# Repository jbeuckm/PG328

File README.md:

# PG328

Program your JX8P/JX10/MKS70 with sliders or MIDI Sysex with this Atmega328 based PG800 variation.

A .96" OLED screen [(buy it here!)](https://amzn.to/4naLiou) shows the status and parameter values and a rotary encoder with momentary push switch provides full PG800 interface capabilities.

### MID SYSEX

#### Prefix: 

* 0x41 // manufacturer ID
* 0x36 // IPR mode
* 0x01 // device ID
* 0x24 // (from MKS70)
* 0x20 // (from MKS70)

#### Suffix:

* 0x01 // Tone

* 0x0F: Reset potentiometer assignments.

### Status:

* 2/24/17: 8-slider pcb tested. This verifies that lots of sliders can work together and will serve as ADSR for EG1 and 2.

* 12/9/16: All Parameters select and display values according to their type. Some even have lil icons...

* 12/7/16: New Sysex message to clear all pot assignments

* 12/3/16: Stable control with encoder. Hold button to rotate parameter or just rotate to change value. Hold button down three seconds to assign slider of highest value to the current parameter.

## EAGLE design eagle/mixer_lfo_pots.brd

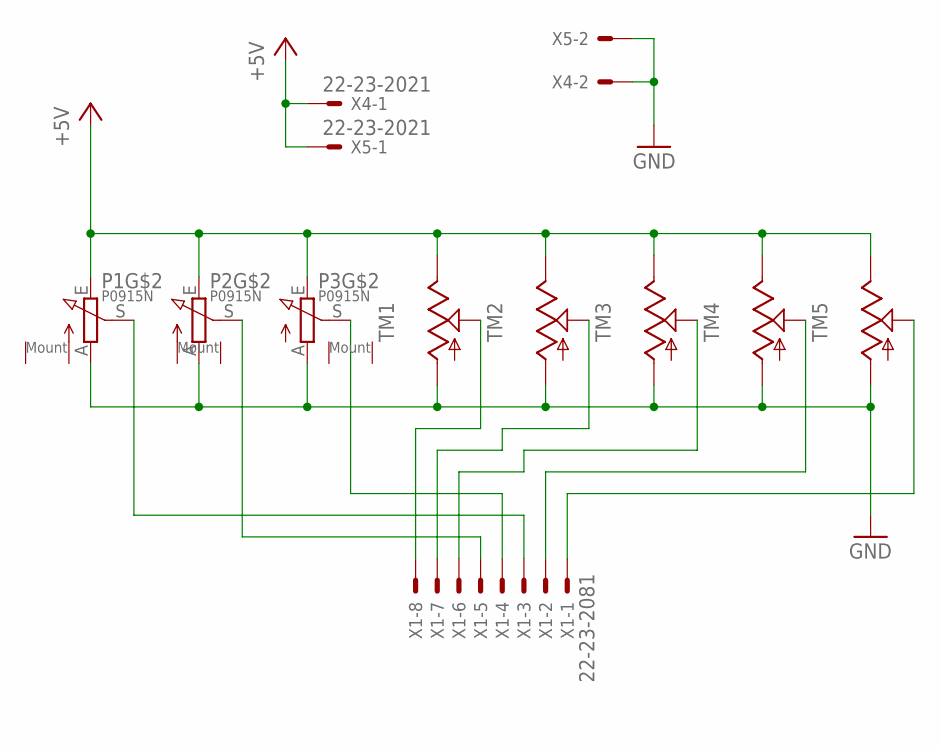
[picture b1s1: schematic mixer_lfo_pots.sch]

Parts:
P1, P2, P3: P0915N
TM1, TM2, TM3, TM4, TM5: TRIMSLIDE60; SLIDEPOT-60
X1: 22-23-2081
X4, X5: 22-23-2021

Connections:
+5V: P1.E, P2.E, P3.E, TM1.B, TM2.B, TM3.B, TM4.B, TM5.B, X4.1, X5.1
GND: P1.A, P2.A, P3.A, TM1.A, TM2.A, TM3.A, TM4.A, TM5.A, X4.2, X5.2
unnamed: P1.S, X1.3
unnamed: P2.S, X1.5
unnamed: P3.S, X1.4
unnamed: TM1.WIPER, X1.8
unnamed: TM2.WIPER, X1.7
unnamed: TM3.WIPER, X1.6
unnamed: TM4.WIPER, X1.2
unnamed: TM5.WIPER, X1.1

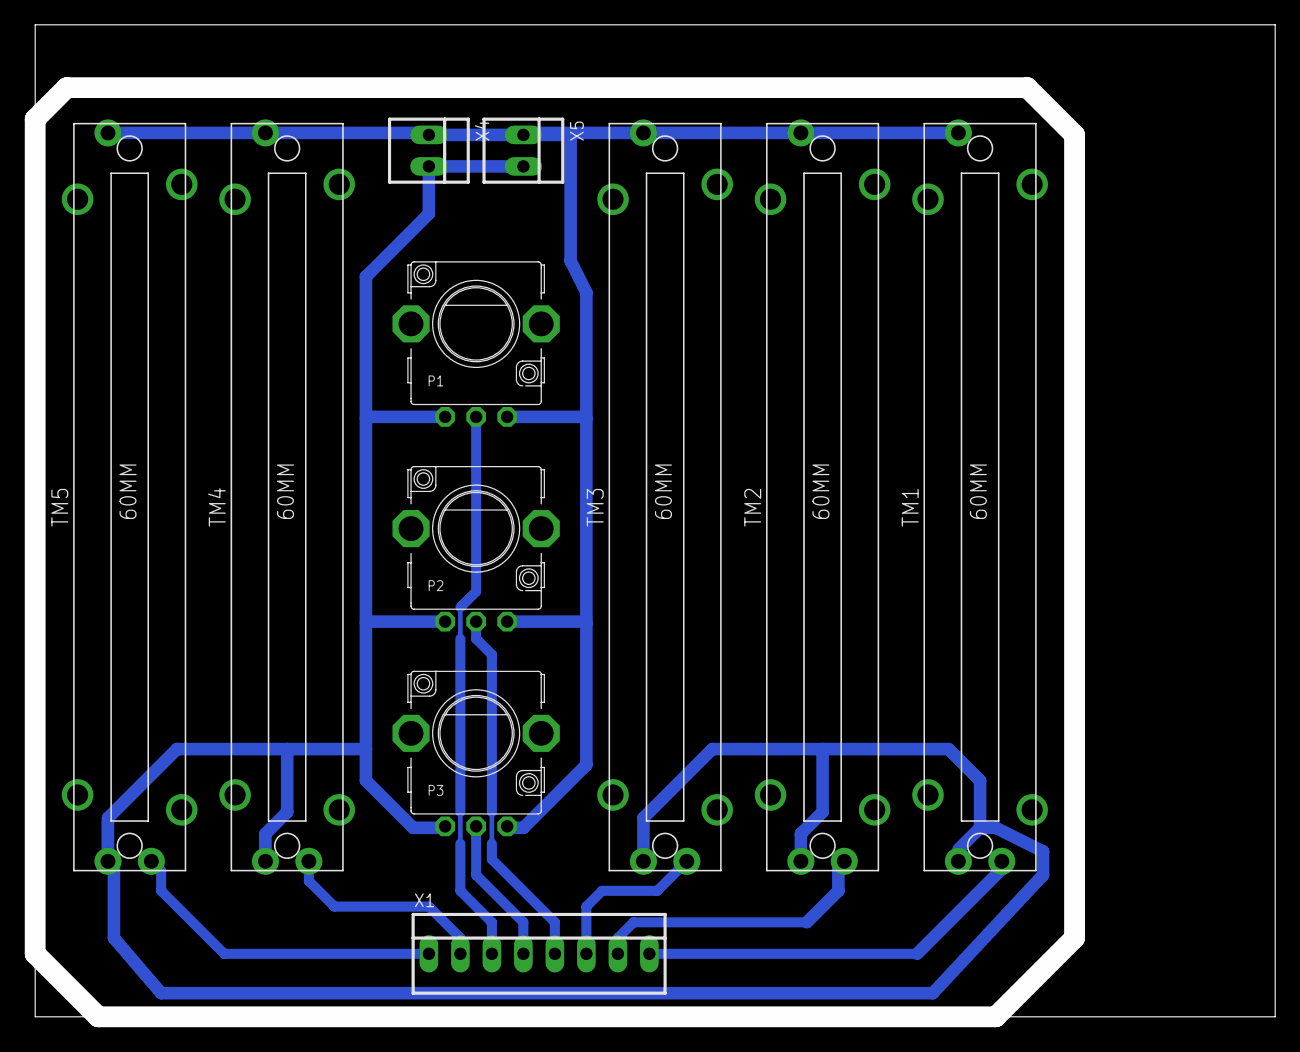
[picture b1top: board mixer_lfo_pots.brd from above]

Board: 2 copper layers, 100.0 x 80.0 mm, 11 parts (0 on the bottom side), 10 nets.

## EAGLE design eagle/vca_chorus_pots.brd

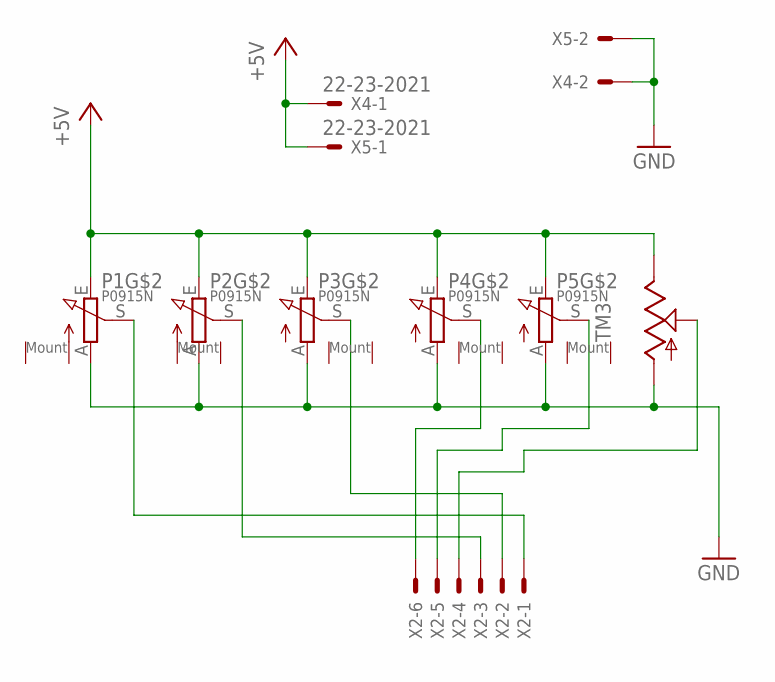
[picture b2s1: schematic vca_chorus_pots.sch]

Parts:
P1, P2, P3, P4, P5: P0915N
TM3: TRIMSLIDE60; SLIDEPOT-60
X2: 22-23-2061
X4, X5: 22-23-2021

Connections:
+5V: P1.E, P2.E, P3.E, P4.E, P5.E, TM3.B, X4.1, X5.1
GND: P1.A, P2.A, P3.A, P4.A, P5.A, TM3.A, X4.2, X5.2
unnamed: P1.S, X2.1
unnamed: P2.S, X2.3
unnamed: P3.S, X2.2
unnamed: P4.S, X2.6
unnamed: P5.S, X2.5
unnamed: TM3.WIPER, X2.4

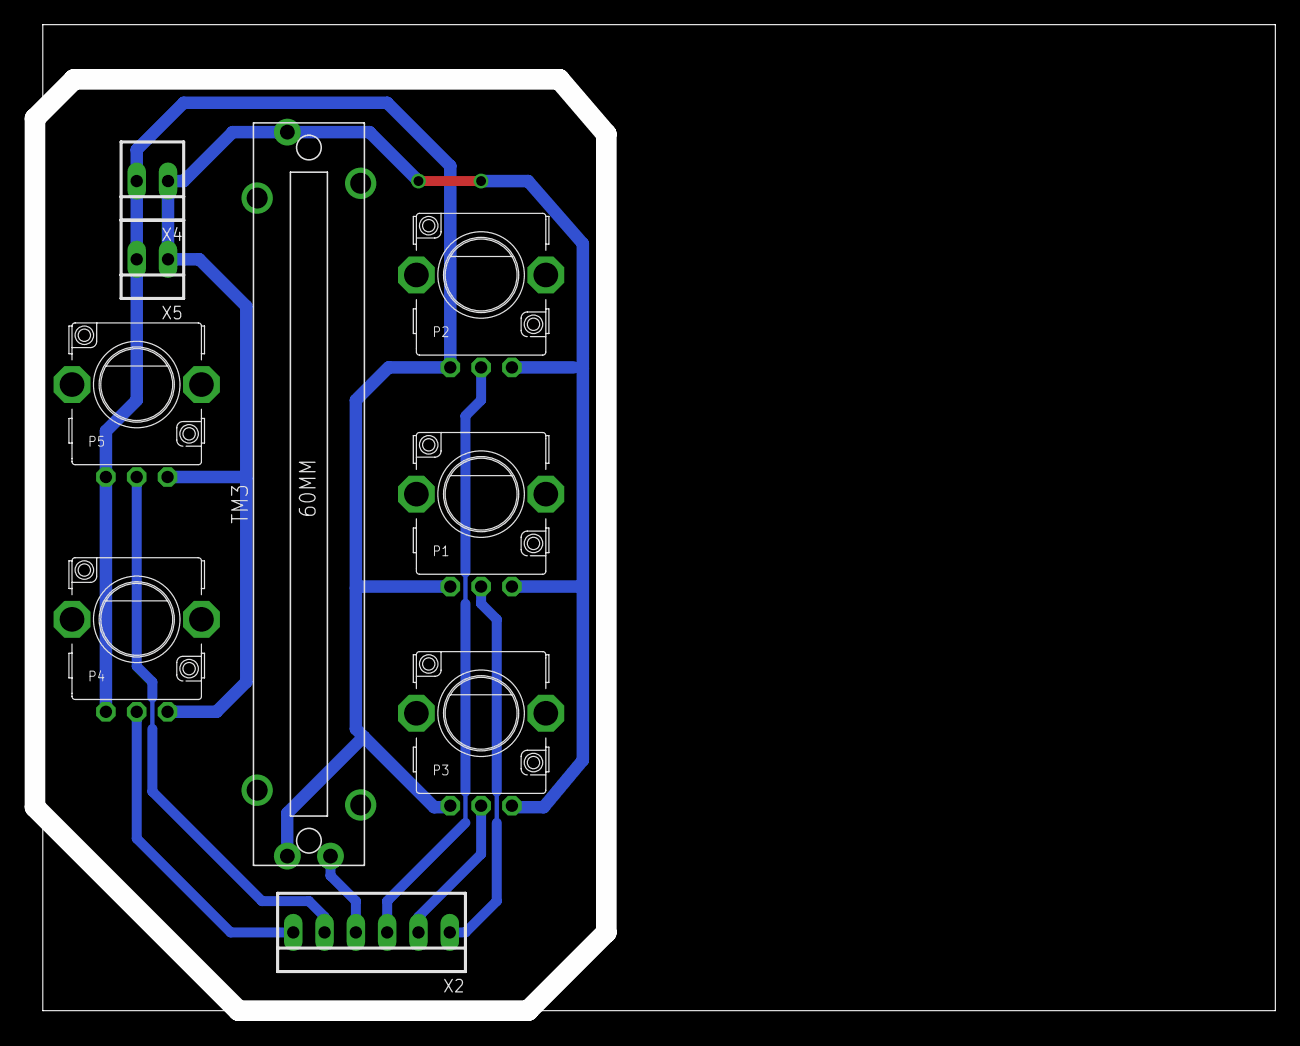
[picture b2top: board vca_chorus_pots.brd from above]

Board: 2 copper layers, 100.6 x 80.0 mm, 9 parts (0 on the bottom side), 8 nets.

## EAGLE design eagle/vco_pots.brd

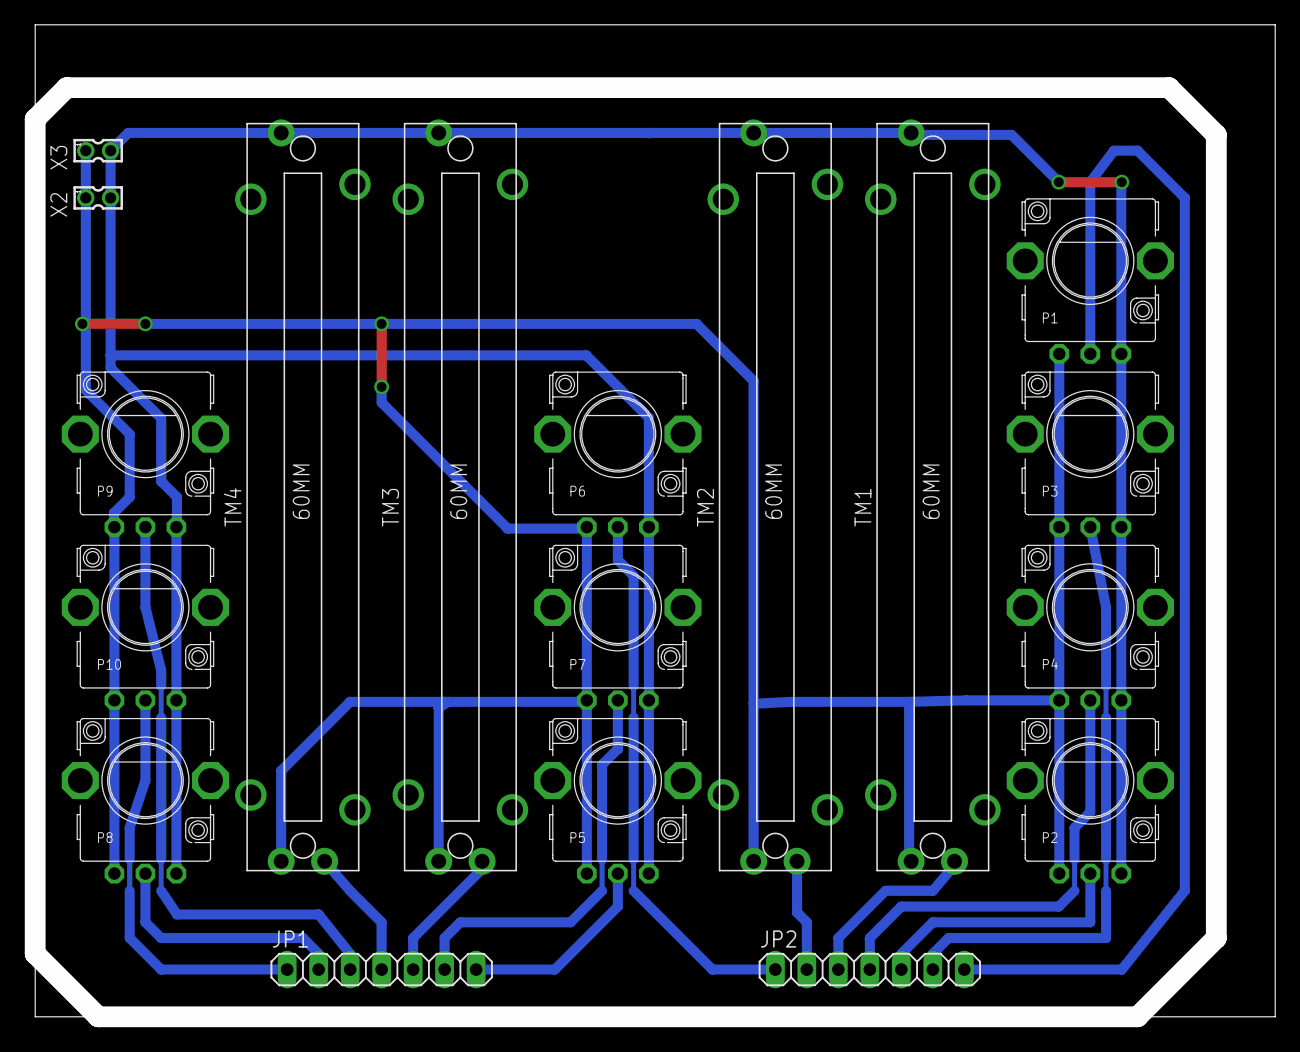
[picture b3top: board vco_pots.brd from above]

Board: 2 copper layers, 100.0 x 80.0 mm, 18 parts (0 on the bottom side), 16 nets.

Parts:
JP1, JP2: 1X07
P1, P2, P3, P4, P5, P6, P7, P8, P9, P10: P0915N
TM1, TM2, TM3, TM4: SLIDEPOT-60
X2, X3: 87758-0216

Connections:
+5V: P1.E, P2.E, P3.E, P4.E, P5.E, P6.E, P7.E, P8.E, P9.E, P10.E, TM1.B, TM2.B, TM3.B, TM4.B, X2.2, X3.2
GND: P1.A, P2.A, P3.A, P4.A, P5.A, P6.A, P7.A, P8.A, P9.A, P10.A, TM1.A, TM2.A, TM3.A, TM4.A, X2.1, X3.1
unnamed: JP1.1, P10.S
unnamed: JP2.1, P6.S
unnamed: JP2.5, P2.S
unnamed: JP1.6, P7.S
unnamed: JP2.6, P3.S
unnamed: JP1.2, P8.S
unnamed: JP1.3, P9.S
unnamed: JP1.7, P5.S
unnamed: JP2.7, P1.S
unnamed: JP2.4, P4.S
unnamed: JP1.4, TM4.WIPER
unnamed: JP1.5, TM3.WIPER
unnamed: JP2.2, TM2.WIPER
unnamed: JP2.3, TM1.WIPER

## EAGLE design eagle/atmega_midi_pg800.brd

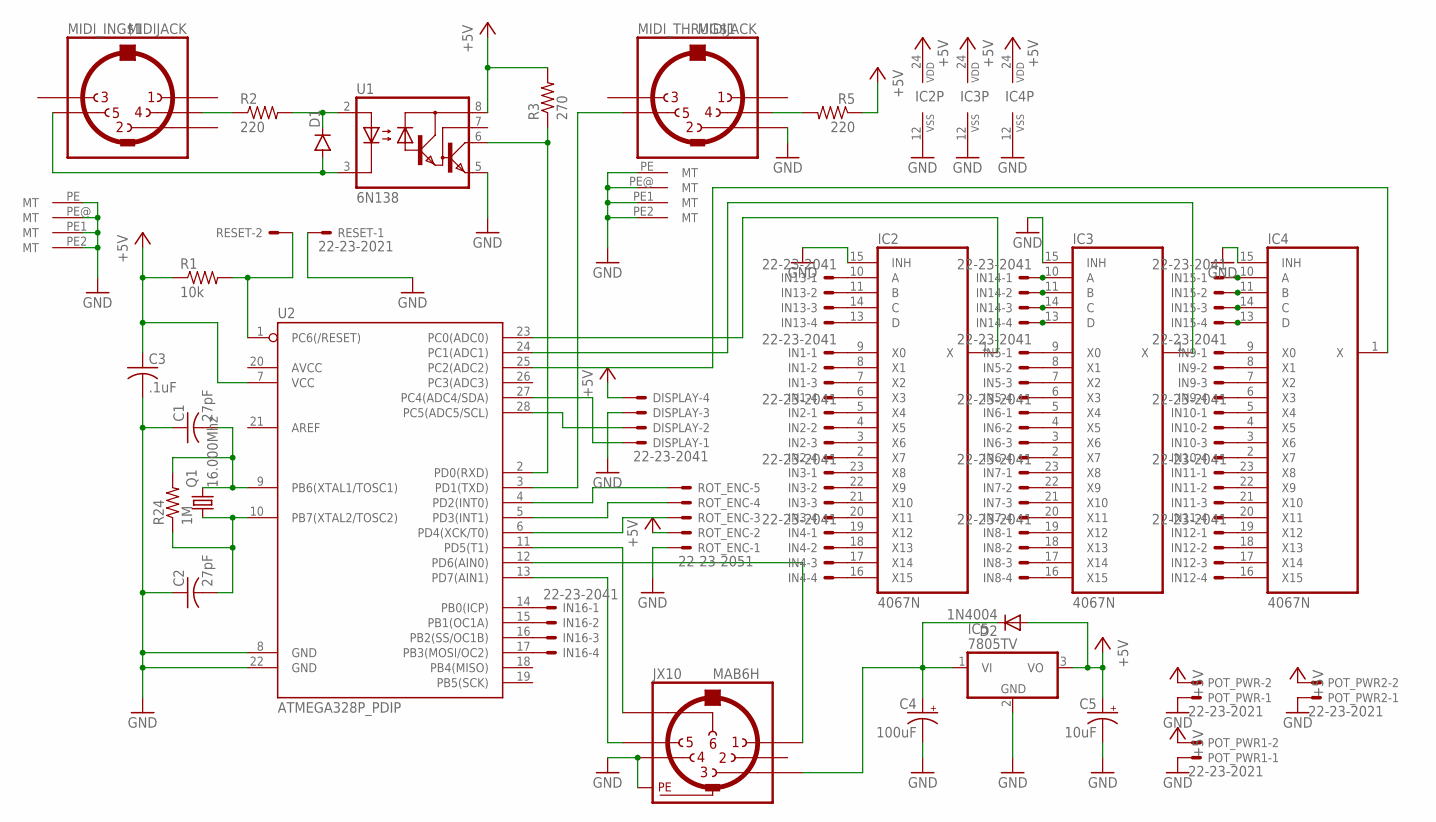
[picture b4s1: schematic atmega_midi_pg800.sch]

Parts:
C1, C2: 27pF; C025-040X050
C3: .1uF; C025-030X050
C4: 100uF; B45181A
C5: 10uF; B45181A
D1: DIODE1N4148; DIODE-1N4148
D2: 1N4004; DO41-10
DISPLAY: 22-23-2041
IC2, IC3, IC4: 4067N; DIL24-6
IC5: 7805TV; TO220V
IN1, IN2, IN3, IN4, IN5, IN6, IN7, IN8, IN9, IN10, IN11, IN12, IN13, IN14, IN15, IN16: 22-23-2041
JX10: MAB6H
MIDI_IN: MIDIJACK; CP-2350
MIDI_THRU: MIDIJACK; CP-2350
POT_PWR, POT_PWR1, POT_PWR2: 22-23-2021
Q1: 16.000Mhz; HC49/S
R1: 10k; 0207/7
R2: 220; 0207/7
R3: 270; 0207/7
R5: 220; 0309/10
R24: 1M; 0207/7
RESET: 22-23-2021
ROT_ENC: 22-23-2051
U1: 6N138; DIL08
U2: ATMEGA328P_PDIP; DIL28-3

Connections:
+5V: C3.1, C5.+, D2.A, DISPLAY.4, IC2.24 (VDD), IC3.24 (VDD), IC4.24 (VDD), IC5.3 (VO), POT_PWR.2, POT_PWR1.2, POT_PWR2.2, R1.1, R3.2, R5.1, ROT_ENC.2, U1.8 (VCC), U2.7 (VCC)
GND: C1.1, C2.1, C3.2, C4.-, C5.-, DISPLAY.3, IC2.12 (VSS), IC2.15 (INH), IC3.12 (VSS), IC3.15 (INH), IC4.12 (VSS), IC4.15 (INH), IC5.2 (GND), JX10.4, JX10.PE, JX10.PE@ (PE), MIDI_IN.PE (MT), MIDI_IN.PE1 (MT), MIDI_IN.PE2 (MT), MIDI_IN.PE@ (MT), MIDI_THRU.2, MIDI_THRU.PE (MT), MIDI_THRU.PE1 (MT), MIDI_THRU.PE2 (MT), MIDI_THRU.PE@ (MT), POT_PWR.1, POT_PWR1.1, POT_PWR2.1, RESET.1, ROT_ENC.1, U1.5 (GND), U2.8 (GND), U2.22 (GND)
unnamed: MIDI_THRU.4, R5.2
unnamed: IC4.1 (X), U2.25 (PC2(ADC2))
unnamed: D1.A, MIDI_IN.5, U1.3 (C)
unnamed: C1.2, Q1.2, R24.2, U2.9 (PB6(XTAL1/TOSC1))
unnamed: C2.2, Q1.1, R24.1, U2.10 (PB7(XTAL2/TOSC2))
unnamed: C4.+, D2.C, IC5.1 (VI), JX10.3
unnamed: D1.C, R2.2, U1.2 (A)
unnamed: MIDI_IN.4, R2.1
unnamed: JX10.6, U2.11 (PD5(T1))
unnamed: JX10.1, U2.12 (PD6(AIN0))
unnamed: JX10.5, U2.13 (PD7(AIN1))
unnamed: DISPLAY.2, U2.28 (PC5(ADC5/SCL))
unnamed: DISPLAY.1, U2.27 (PC4(ADC4/SDA))
unnamed: IC3.1 (X), U2.24 (PC1(ADC1))
unnamed: IC2.1 (X), U2.23 (PC0(ADC0))
unnamed: IN16.1, U2.14 (PB0(ICP))
unnamed: IN16.2, U2.15 (PB1(OC1A))
unnamed: IC3.10 (A), IN14.1
unnamed: IC3.11 (B), IN14.2
unnamed: IC2.9 (X0), IN1.1
unnamed: IC2.8 (X1), IN1.2
unnamed: IC2.7 (X2), IN1.3
unnamed: IC2.6 (X3), IN1.4
unnamed: IC2.5 (X4), IN2.1
unnamed: IC2.4 (X5), IN2.2
unnamed: IC2.3 (X6), IN2.3
unnamed: IC2.2 (X7), IN2.4
unnamed: IC2.23 (X8), IN3.1
unnamed: IC2.22 (X9), IN3.2
unnamed: R3.1, U1.6 (VO), U2.2 (PD0(RXD))
unnamed: IC2.21 (X10), IN3.3
unnamed: IC2.20 (X11), IN3.4
unnamed: IC2.19 (X12), IN4.1
unnamed: IC2.18 (X13), IN4.2
unnamed: IC2.17 (X14), IN4.3
unnamed: IC2.16 (X15), IN4.4
unnamed: IC3.9 (X0), IN5.1
unnamed: IC3.8 (X1), IN5.2
unnamed: IC3.7 (X2), IN5.3
unnamed: IC3.6 (X3), IN5.4
unnamed: IC3.5 (X4), IN6.1
unnamed: MIDI_THRU.5, U2.3 (PD1(TXD))
unnamed: R1.2, RESET.2, U2.1 (PC6(/RESET))
unnamed: IC3.4 (X5), IN6.2
unnamed: IC3.3 (X6), IN6.3
unnamed: IC3.2 (X7), IN6.4
unnamed: IC3.23 (X8), IN7.1
unnamed: IC3.22 (X9), IN7.2
unnamed: IC3.21 (X10), IN7.3
unnamed: IC3.20 (X11), IN7.4
unnamed: IC3.19 (X12), IN8.1
unnamed: IC3.18 (X13), IN8.2
unnamed: IC3.17 (X14), IN8.3
unnamed: IC3.16 (X15), IN8.4
unnamed: IC4.9 (X0), IN9.1
unnamed: IC4.8 (X1), IN9.2
unnamed: IC4.7 (X2), IN9.3
unnamed: IC4.6 (X3), IN9.4
unnamed: IC4.5 (X4), IN10.1
unnamed: IC4.4 (X5), IN10.2
unnamed: IC4.3 (X6), IN10.3
unnamed: IC4.2 (X7), IN10.4
unnamed: IC4.23 (X8), IN11.1
unnamed: IC4.22 (X9), IN11.2
unnamed: IC4.21 (X10), IN11.3
unnamed: IC4.20 (X11), IN11.4
unnamed: IC4.19 (X12), IN12.1
unnamed: IC4.18 (X13), IN12.2
unnamed: IC4.17 (X14), IN12.3
unnamed: IC4.16 (X15), IN12.4
unnamed: IC3.14 (C), IN14.3
unnamed: IC3.13 (D), IN14.4
unnamed: IC4.10 (A), IN15.1
unnamed: IC4.11 (B), IN15.2
unnamed: IC4.14 (C), IN15.3
unnamed: IC4.13 (D), IN15.4
unnamed: IN16.3, U2.16 (PB2(SS/OC1B))
unnamed: IN16.4, U2.17 (PB3(MOSI/OC2))
unnamed: IC2.13 (D), IN13.4
unnamed: IC2.14 (C), IN13.3
unnamed: IC2.11 (B), IN13.2
unnamed: IC2.10 (A), IN13.1
unnamed: ROT_ENC.5, U2.4 (PD2(INT0))
unnamed: ROT_ENC.4, U2.5 (PD3(INT1))
unnamed: ROT_ENC.3, U2.6 (PD4(XCK/T0))

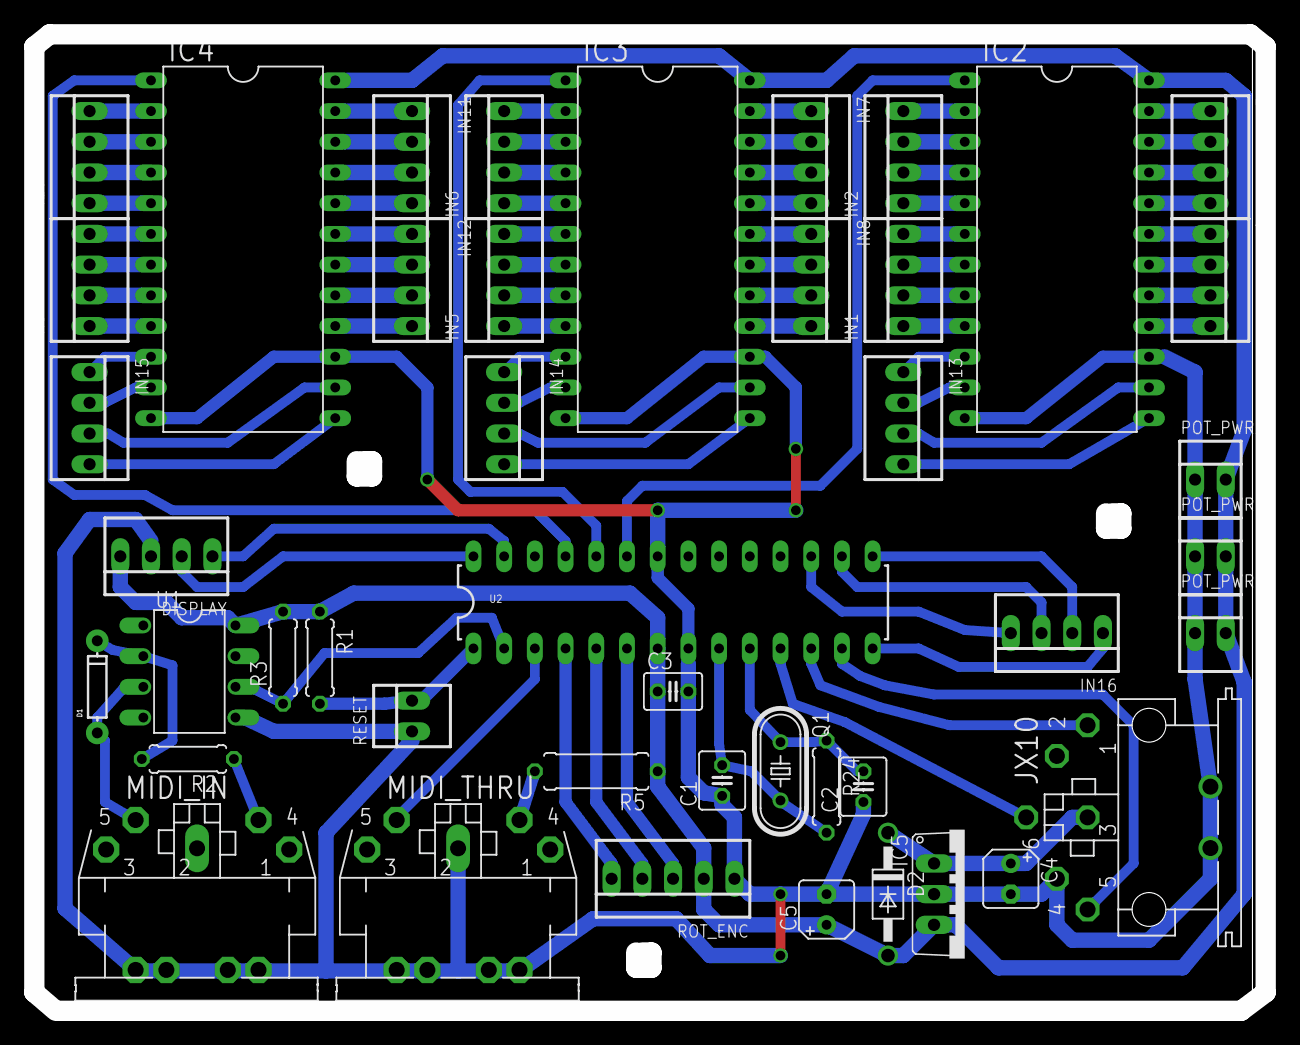
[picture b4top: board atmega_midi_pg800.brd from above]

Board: 2 copper layers, 101.9 x 80.8 mm, 44 parts (0 on the bottom side), 87 nets.

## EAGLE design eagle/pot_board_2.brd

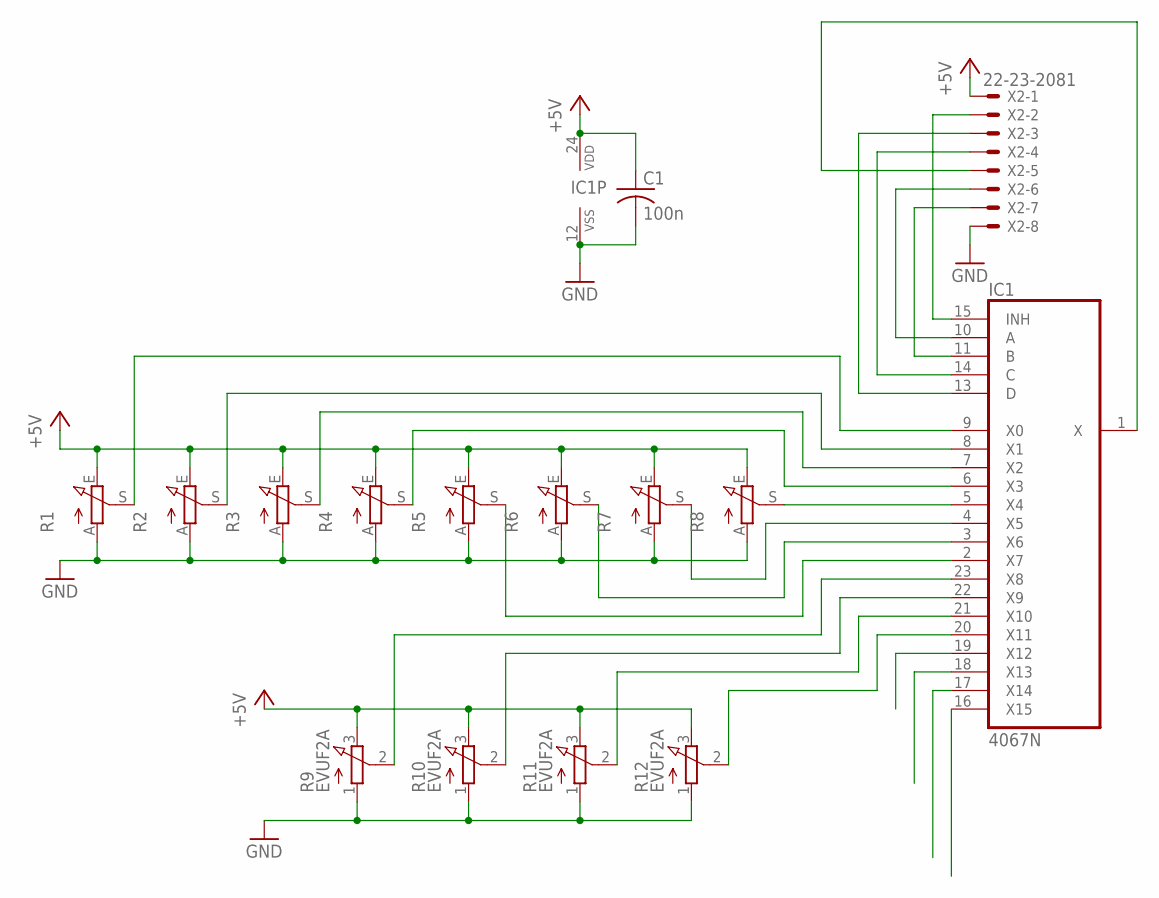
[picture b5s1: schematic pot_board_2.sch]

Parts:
C1: 100n; C025-024X044
IC1: 4067N; DIL24-6
R1, R2, R3, R4, R5, R6, R7, R8: 3RP/1610N45MM-SLIDE; ST15
R9, R10, R11, R12: EVUF2A; EVUF
X2: 22-23-2081

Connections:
+5V: C1.1, IC1.24 (VDD), R1.E, R2.E, R3.E, R4.E, R5.E, R6.E, R7.E, R8.E, R9.3 (E), R10.3 (E), R11.3 (E), R12.3 (E), X2.1
GND: C1.2, IC1.12 (VSS), R1.A, R2.A, R3.A, R4.A, R5.A, R6.A, R7.A, R8.A, R9.1 (A), R10.1 (A), R11.1 (A), R12.1 (A), X2.8
unnamed: IC1.9 (X0), R1.S
unnamed: IC1.8 (X1), R2.S
unnamed: IC1.7 (X2), R3.S
unnamed: IC1.6 (X3), R4.S
unnamed: IC1.5 (X4), R8.S
unnamed: IC1.4 (X5), R7.S
unnamed: IC1.3 (X6), R6.S
unnamed: IC1.2 (X7), R5.S
unnamed: IC1.15 (INH), X2.2
unnamed: IC1.23 (X8), R9.2 (S)
unnamed: IC1.11 (B), X2.7
unnamed: IC1.10 (A), X2.6
unnamed: IC1.14 (C), X2.4
unnamed: IC1.13 (D), X2.3
unnamed: IC1.1 (X), X2.5
unnamed: IC1.22 (X9), R10.2 (S)
unnamed: IC1.21 (X10), R11.2 (S)
unnamed: IC1.20 (X11), R12.2 (S)

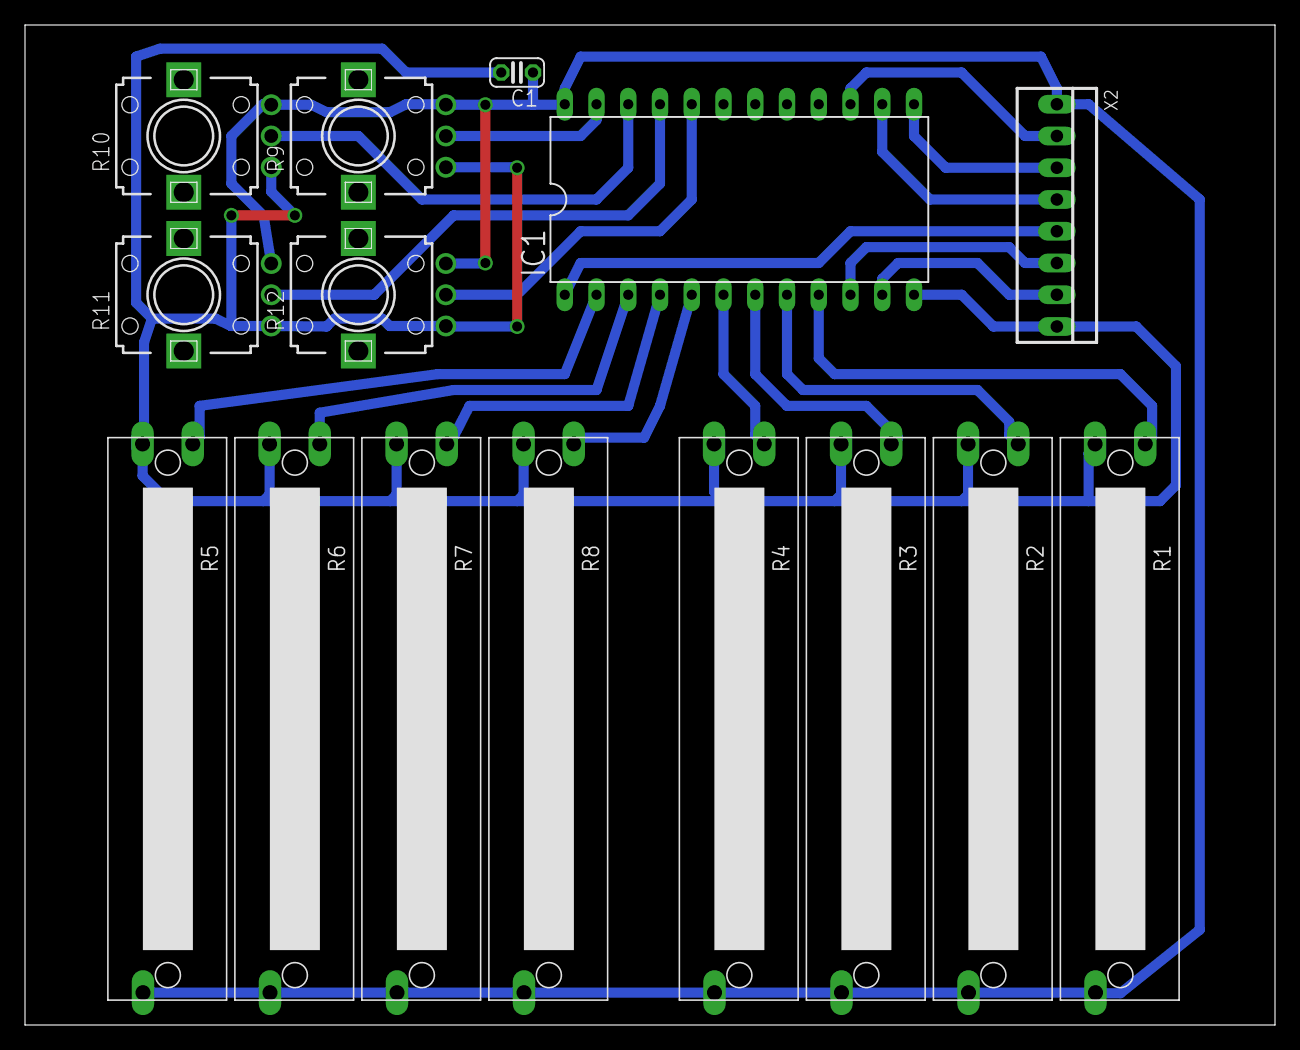
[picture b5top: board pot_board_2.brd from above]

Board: 2 copper layers, 100.0 x 80.0 mm, 15 parts (0 on the bottom side), 20 nets.

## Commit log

2016-11-15 function to write a byte like PG800
2016-11-15 porting up to atmega328 for arduino compat etc
2016-11-16 starting eagle schemo
2016-11-16 routed
2016-11-16 gcode
2016-11-17 16 sliders
2016-11-17 added oled disply connection
2016-11-17 mux coming in
2016-11-17 muxes with input holes
2016-11-17 input terminals wired
2016-11-17 placement improved
2016-11-17 placed again
2016-11-18 standard connector for display
2016-11-18 rotary encoder connection
2016-11-18 cutout
2016-11-18 big boy version of 7805 to power those 4067 and the display
2016-11-18 protectoin diode and pot power hookups
2016-11-19 tried gcode
2016-11-20 moved a resistor away from midi in jack
2016-11-25 running rotary encoder and oled screen
2016-11-25 class to emulate pg800
2016-11-25 rectangles
2016-11-25 initializing encoder with a switch pin
2016-11-26 button callbacks
2016-11-26 rotate callbacks
2016-11-26 control mode with param and value changes
2016-11-26 less mem
2016-11-26 param names into program memory
2016-11-26 change param while button down
2016-11-26 set param and value from sysex
2016-11-26 refactored controlMode to changeParam
2016-11-26 started some averaging code
2016-11-28 corrected mask to start on bit 7
2016-11-29 negative pg800 data line and send first bytes on dec
2016-11-29 fixed pg800 interface pins
2016-11-29 ignore flags for each pot and send pg800 data for inc dec and set
2016-11-30 mks70 sysex midi in works
2016-12-03 display update when needed
2016-12-03 5us delay after sending data
2016-12-03 pot assignment display
2016-12-03 direction reversed and pot not ignored
2016-12-03 stub function for sync
2016-12-03 established compact bool array for param changed flags
2016-12-03 pretty stable with volatiles marked
2016-12-03 pretty good with sync function working
2016-12-03 detaching encoder interrupt during display update and no lockups
2016-12-03 circular out buffer and one byte at a time
2016-12-03 move encoder interrupt toggling into main loop and faster averaging
2016-12-03 readme updated with image
2016-12-03 pcb layout
2016-12-03 ignore sysex device id for now
2016-12-05 potAssigned is byte, new rounding loop for pots, ignore sysex device id
2016-12-06 send both bytes on sync and average over eight readings
2016-12-06 macros for checking pots
2016-12-06 no flutter but can't see 0
2016-12-06 defined value for no new pot assignment, ignorePot becomes potEnabled and pot zero position handled specifically
2016-12-06 EEPROM saving assignments and quick delay when assigning
2016-12-06 sysex command to reset pot assignments
2016-12-06 compiles with new class
2016-12-07 established param type function array mechanism for typing out params
2016-12-07 draw value into param type function
2016-12-07 paramTypes into PROGMEM and second type functions established
2016-12-07 four val param type works
2016-12-07 range and wave param types
2016-12-07 xmod param type
2016-12-07 general string drawing function for 4val param types
2016-12-07 eg mode draw function
2016-12-08 eg mode works
2016-12-09 tune, fine, vca eg mode, lfo wave, chorus param types
2016-12-09 all params typed
2017-02-19 testing library for the sliders i bought
2017-02-25 slider board
2017-02-26 working up 14 pots for vco controls
2017-02-26 schemo wired
2017-02-26 cutout for vco controls
2017-02-26 corrected jumper between sliders
2017-02-26 moved pcb to zero corner
2017-02-28 vcf pot board
2017-03-05 routed vca pot brd
2017-03-06 the last pcb
2017-03-10 panel shape
2017-03-11 knobs
2017-03-15 panel labels begin
2017-03-15 section labels
2017-03-15 filter labels
2017-03-16 labels in
2017-03-16 mounting holes
2017-03-23 panel text tweaked and vectored

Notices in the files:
parts and their libraries:
SparkFun-DiscreteSemi: Licensing: Creative Commons ShareAlike 4.0 International - https://creativecommons.org/licenses/by-sa/4.0
